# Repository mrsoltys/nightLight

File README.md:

# nightLight

A Particle project named nightLight

## Welcome to your project!

Every new Particle project is composed of 3 important elements that you'll see have been created in your project directory for nightLight.

#### ```/src``` folder:  
This is the source folder that contains the firmware files for your project. It should *not* be renamed. 
Anything that is in this folder when you compile your project will be sent to our compile service and compiled into a firmware binary for the Particle device that you have targeted.

If your application contains multiple files, they should all be included in the `src` folder. If your firmware depends on Particle libraries, those dependencies are specified in the `project.properties` file referenced below.

#### ```.ino``` file:
This file is the firmware that will run as the primary application on your Particle device. It contains a `setup()` and `loop()` function, and can be written in Wiring or C/C++. For more information about using the Particle firmware API to create firmware for your Particle device, refer to the [Firmware Reference](https://docs.particle.io/reference/firmware/) section of the Particle documentation.

#### ```project.properties``` file:  
This is the file that specifies the name and version number of the libraries that your project depends on. Dependencies are added automatically to your `project.properties` file when you add a library to a project using the `particle library add` command in the CLI or add a library in the Desktop IDE.

## Adding additional files to your project

#### Projects with multiple sources
If you would like add additional files to your application, they should be added to the `/src` folder. All files in the `/src` folder will be sent to the Particle Cloud to produce a compiled binary.

#### Projects with external libraries
If your project includes a library that has not been registered in the Particle libraries system, you should create a new folder named `/lib/<libraryname>/src` under `/<project dir>` and add the `.h`, `.cpp` & `library.properties` files for your library there. Read the [Firmware Libraries guide](https://docs.particle.io/guide/tools-and-features/libraries/) for more details on how to develop libraries. Note that all contents of the `/lib` folder and subfolders will also be sent to the Cloud for compilation.

## Compiling your project

When you're ready to compile your project, make sure you have the correct Particle device target selected and run `particle compile <platform>` in the CLI or click the Compile button in the Desktop IDE. The following files in your project folder will be sent to the compile service:

- Everything in the `/src` folder, including your `.ino` application file
- The `project.properties` file for your project
- Any libraries stored under `lib/<libraryname>/src`

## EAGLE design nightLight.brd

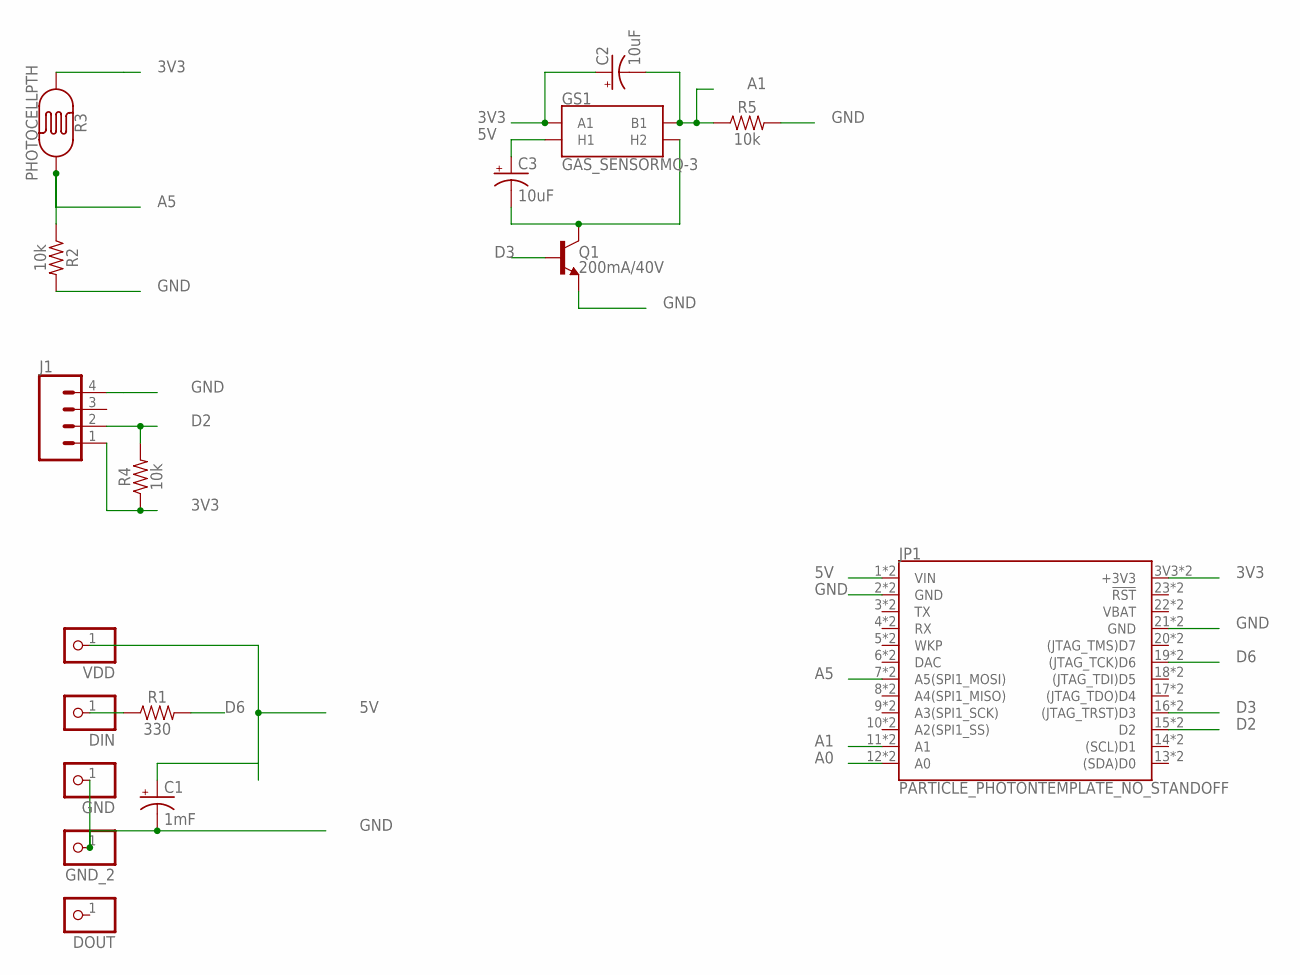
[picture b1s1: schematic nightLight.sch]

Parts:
C1: 1mF; CPOL-RADIAL-5MM-10MM
C2, C3: 10uF; CPOL-RADIAL-2.5MM-5MM
DIN: PINHD-1X1CB; 1X01-CLEANBIG
DOUT: PINHD-1X1CB; 1X01-CLEANBIG
GND: PINHD-1X1CB; 1X01-CLEANBIG
GND_2: PINHD-1X1CB; 1X01-CLEANBIG
GS1: GAS_SENSORMQ-3; GAS_SENSOR
J1: CONN_04; 1X04
JP1: PARTICLE_PHOTONTEMPLATE_NO_STANDOFF; PARTICLE_PHOTON_TEMPLATE_NO_STANDOFF
Q1: 200mA/40V; TO-92-EZ
R1: 330; AXIAL-0.3
R2, R4, R5: 10k; AXIAL-0.3
R3: PHOTOCELLPTH; PHOTOCELL
VDD: PINHD-1X1CB; 1X01-CLEANBIG

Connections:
3V3: C2.1 (+), GS1.A1, J1.1, JP1.3V3 (+3V3), JP1.24 (+3V3), R3.1, R4.P$1 (1)
5V: C1.+, C3.1 (+), GS1.HA (H1), JP1.1 (VIN), JP1.VIN, VDD.1
A0: JP1.12 (A0), JP1.A0
A1: C2.2 (-), GS1.B1, JP1.11 (A1), JP1.A1, R5.P$1 (1)
A5: JP1.7 (A5(SPI1_MOSI)), JP1.A5 (A5(SPI1_MOSI)), R2.P$1 (1), R3.2
D2: J1.2, JP1.15 (D2), JP1.D2, R4.P$2 (2)
D3: JP1.16 ((JTAG_TRST)D3), JP1.D3 ((JTAG_TRST)D3), Q1.2 (B)
D6: JP1.19 ((JTAG_TCK)D6), JP1.D6 ((JTAG_TCK)D6), R1.P$2 (2)
GND: C1.-, GND.1, GND_2.1, J1.4, JP1.2 (GND), JP1.21 (GND), JP1.GND@0 (GND), JP1.GND@2 (GND), Q1.1 (E), R2.P$2 (2), R5.P$2 (2)
unnamed: DIN.1, R1.P$1 (1)
unnamed: C3.2 (-), GS1.HB (H2), Q1.3 (C)
VBAT: JP1.22 (VBAT), JP1.VBAT

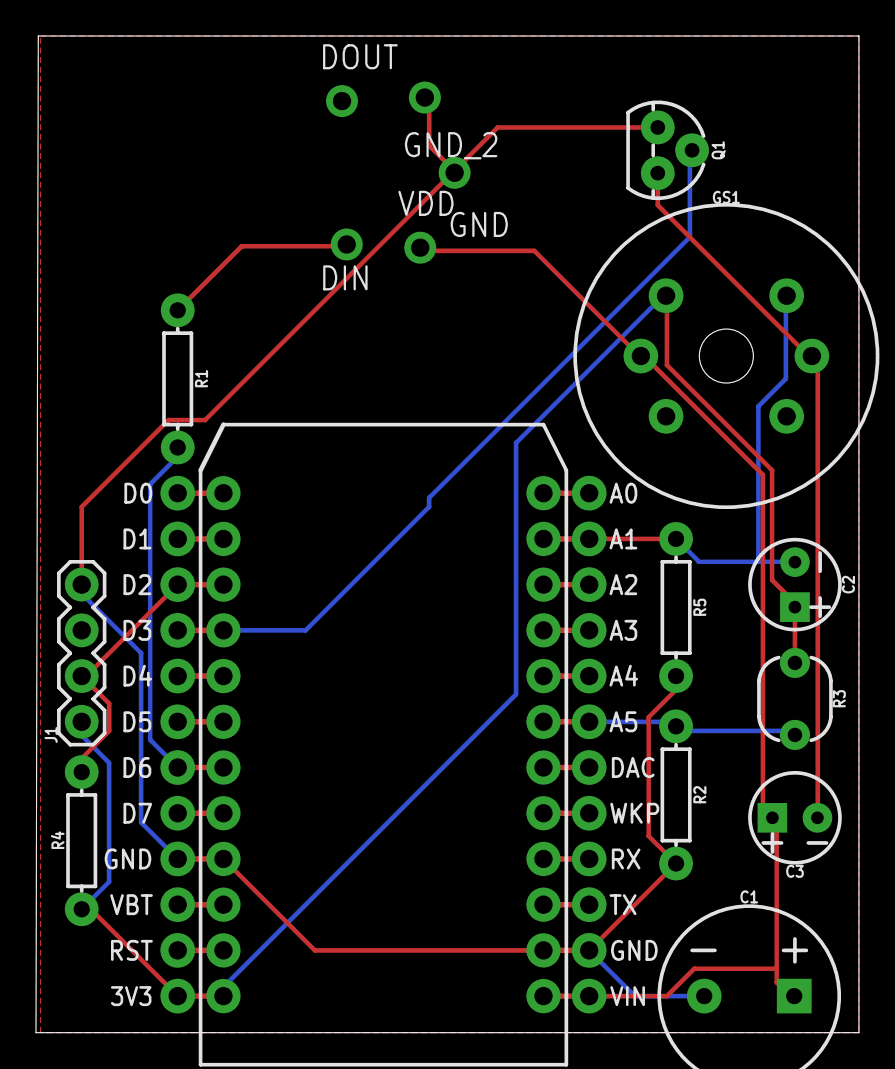
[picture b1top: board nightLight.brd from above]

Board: 2 copper layers, 45.7 x 55.4 mm, 17 parts (0 on the bottom side), 12 nets.

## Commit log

2018-10-11 Working on hooking up MQ-07 CO sensor
2018-10-12 Finished MQ07 Hookup
2018-10-19 This is the board i ordered
2018-10-24 Added code
2018-11-10 added CO sensor code
2020-03-06 Worked on combining night light code with smart clock code.
    Clock will go on Pins 0, 1, 4, and 5 (double check in morning)
2020-03-06 changed order of weather LEDs
2020-03-06 updated color scheme
2020-03-06 Updated Color Scale
2020-03-06 fixed typo
2020-03-06 binaries
2020-04-10 Fixed timezone issue
2020-04-10 Converted to particle project to help with library management remotely

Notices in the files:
parts and their libraries:
SparkFun-Capacitors: Licensing: Creative Commons ShareAlike 4.0 International - https://creativecommons.org/licenses/by-sa/4.0
